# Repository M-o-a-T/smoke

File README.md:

# Fire Detector

## Gira

The "Gira" board is intended to plug into a "Gira Dual" smoke detector.
This device (30€) has a thermometer as well as a smoke chamber, a
serial interface that's actually useful, and the ability to run on 12V
external as well as 9V battery power.

It runs on 3.3V; the 1wire bus (5V) is connected via a level shifter.

Code will be in https://github.com/M-o-a-T/owslave

## Funk

The "Funk" board is a small (and currently untested) board that connects
a cheap smoke detector to RF. There's no code for it.

## Programming

The programming interface is a standard 6-pin plug, except that it's
used via a 3x2 pogo plug. If you need to attach a 6-pin header, soldering
that to the top of the pads is fairly easy. You should add some
two-component glue after soldering so that you won't pull the pads off when
you unplug.

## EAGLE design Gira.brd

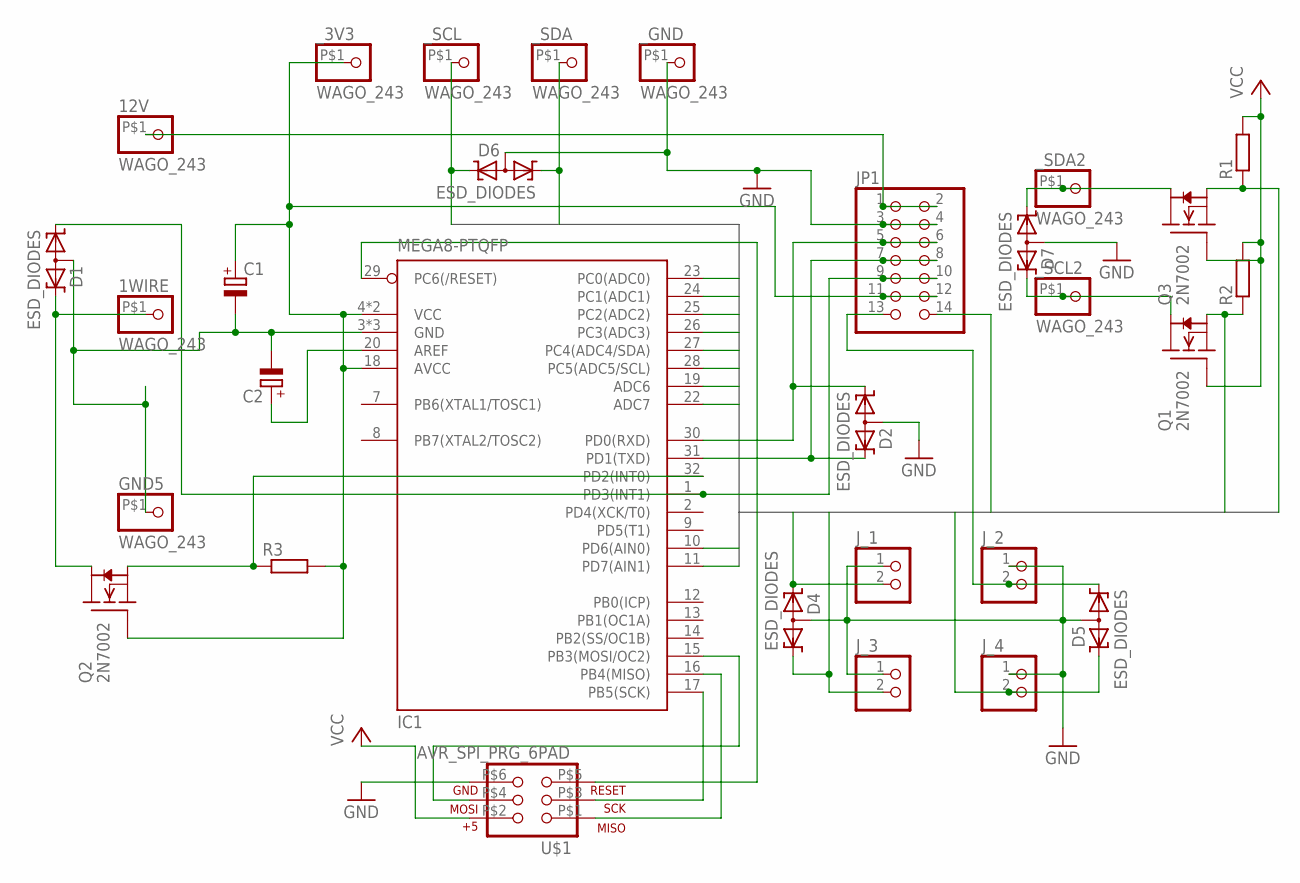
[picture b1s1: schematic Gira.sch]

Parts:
1WIRE, 12V: WAGO_243
C1, C2: CP1206
D1, D2, D4, D5, D6, D7: ESD_DIODES; SOT23
GND5: WAGO_243
IC1: MEGA8-PTQFP; TQFP32-08
JP1: PINHD-2X7; 2X07
J_1, J_2, J_3, J_4: PINHD-1X2LEVER; 1X02_GN
Q1, Q2, Q3: 2N7002; SOT23
R1, R2, R3: R-EU_R0603; R0603
U$1: AVR_SPI_PRG_6PAD; 2X3_PAD
_3V3: WAGO_243
_GND: WAGO_243
_SCL, _SCL2: WAGO_243
_SDA, _SDA2: WAGO_243

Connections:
3V3: C1.+, IC1.4 (VCC), IC1.6 (VCC), IC1.18 (AVCC), JP1.11, JP1.12, Q2.1 (G), R3.2, U$1.P$2 (2), _3V3.P$1
B1: D4.2 (K2), IC1.23 (PC0(ADC0)), J_1.2
B2: D5.1 (K1), IC1.24 (PC1(ADC1)), J_2.2
B3: D4.1 (K1), IC1.25 (PC2(ADC2)), J_3.2
B4: D5.2 (K2), IC1.26 (PC3(ADC3)), J_4.2
GND: C1.-, C2.-, D1.3 (AA), D2.3 (AA), D4.3 (AA), D5.3 (AA), D6.3 (AA), D7.3 (AA), GND5.P$1, IC1.3 (GND), IC1.5 (GND), IC1.21 (GND), JP1.3, JP1.4, J_1.1, J_2.1, J_3.1, J_4.1, U$1.P$6 (6), _GND.P$1
unnamed: C2.+, IC1.20 (AREF)
unnamed: IC1.32 (PD2(INT0)), Q2.2 (S), R3.1
unnamed: 1WIRE.P$1, D1.2 (K2), Q2.3 (D)
unnamed: D7.1 (K1), Q3.3 (D), _SDA2.P$1
unnamed: D7.2 (K2), Q1.3 (D), _SCL2.P$1
unnamed: IC1.15 (PB3(MOSI/OC2)), U$1.P$4 (4)
unnamed: IC1.16 (PB4(MISO)), U$1.P$1 (1)
unnamed: IC1.17 (PB5(SCK)), U$1.P$3 (3)
unnamed: IC1.29 (PC6(/RESET)), U$1.P$5 (5)
unnamed: 12V.P$1, JP1.1, JP1.2
unnamed: D2.2 (K2), IC1.31 (PD1(TXD)), JP1.7, JP1.8
unnamed: D2.1 (K1), IC1.30 (PD0(RXD)), JP1.5, JP1.6
unnamed: D1.1 (K1), IC1.1 (PD3(INT1)), JP1.9, JP1.10
RESET: IC1.10 (PD6(AIN0)), JP1.13
SCL: D6.2 (K2), IC1.22 (ADC7), _SCL.P$1
SCL2: IC1.28 (PC5(ADC5/SCL)), Q1.2 (S), R2.1
SDA: D6.1 (K1), IC1.19 (ADC6), _SDA.P$1
SDA2: IC1.27 (PC4(ADC4/SDA)), Q3.2 (S), R1.1
TEST: IC1.11 (PD7(AIN1)), JP1.14
VCC: Q1.1 (G), Q3.1 (G), R1.2, R2.2

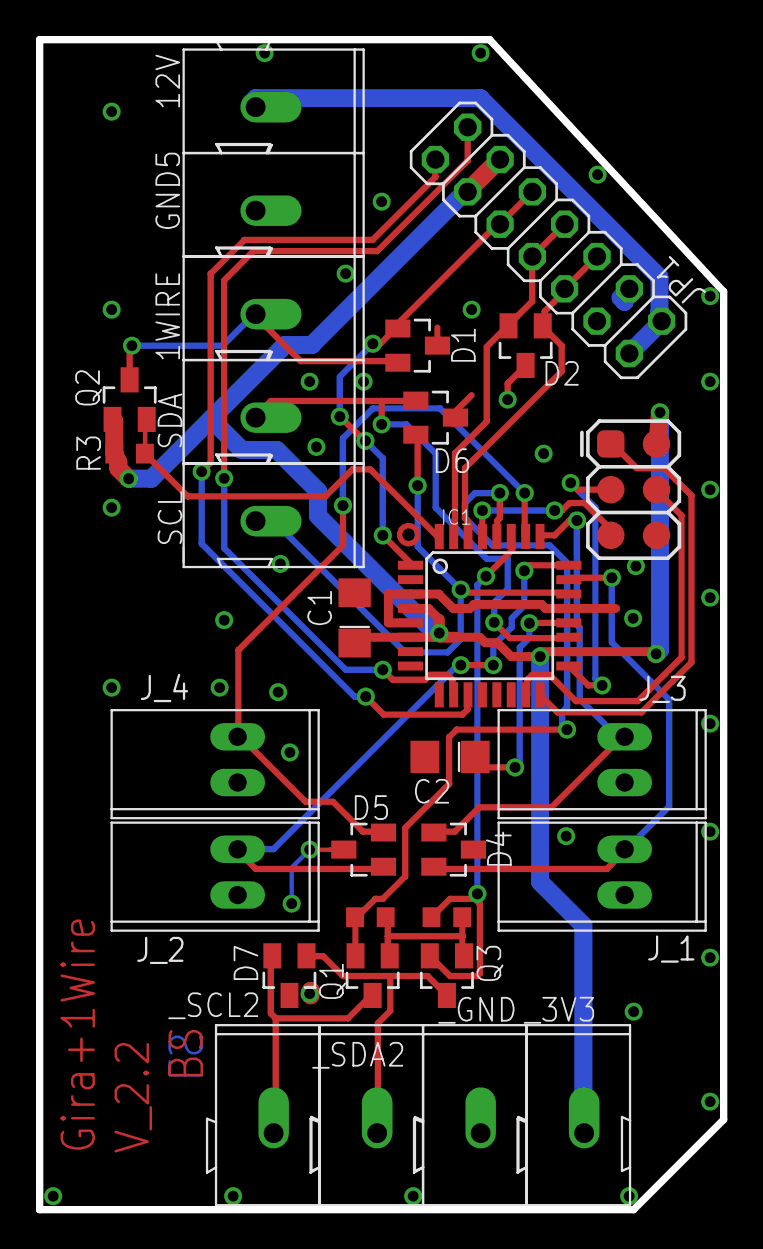
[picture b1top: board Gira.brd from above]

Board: 2 copper layers, 38.0 x 65.0 mm, 30 parts (0 on the bottom side), 26 nets.

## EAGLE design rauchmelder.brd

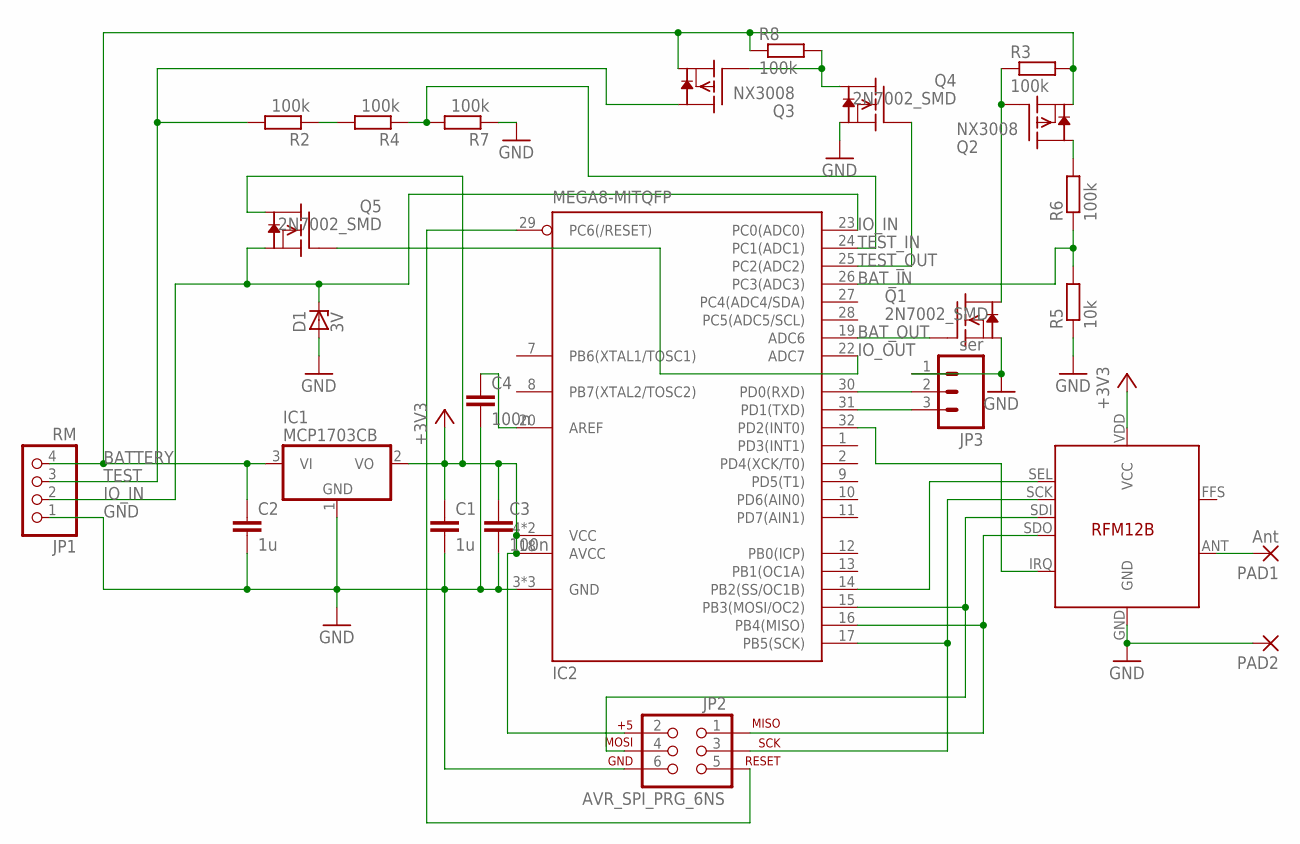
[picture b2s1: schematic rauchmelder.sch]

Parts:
C1, C2: 1u; C0603
C3, C4: 100n; C0603
D1: 3V; SOD80C
IC1: MCP1703CB; SOT23
IC2: MEGA8-MITQFP; TQFP32-08
IC3: RFM12B; MPN RFM12B-868-S1
JP1: RM; 1X04
JP2: AVR_SPI_PRG_6NS; 2X3-NS
JP3: ser; 1X03
PAD1: Ant; 1,6/0,8
PAD2: 1,6/0,8
Q1, Q4, Q5: 2N7002_SMD; SOT23
Q2, Q3: NX3008; SOT23; MPN NX3008NBK
R2, R3, R4, R6, R7, R8: 100k; R0603
R5: 10k; R0603

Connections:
+3V3: C1.1, C3.1, IC1.2 (VO), IC2.4 (VCC), IC2.6 (VCC), IC2.18 (AVCC), IC3.VDD (VCC), JP2.2, Q5.3 (D)
BATTERY: C2.1, IC1.3 (VI), JP1.4, Q2.2 (S), Q3.2 (S), R3.2, R8.1
BAT_IN: IC2.26 (PC3(ADC3)), R5.2, R6.1
BAT_OUT: IC2.19 (ADC6), Q1.1 (G)
GND: C1.2, C2.2, C3.2, C4.2, D1.A, IC1.1 (GND), IC2.3 (GND), IC2.5 (GND), IC2.21 (GND), IC3.GND, JP1.1, JP2.6, JP3.1, PAD2.1, Q1.2 (S), Q4.2 (S), R5.1, R7.1
IO_IN: D1.C, IC2.23 (PC0(ADC0)), JP1.2, Q5.2 (S)
IO_OUT: IC2.22 (ADC7), Q5.1 (G)
unnamed: R2.1, R4.2
unnamed: IC2.29 (PC6(/RESET)), JP2.5
unnamed: Q2.3 (D), R6.2
unnamed: IC2.16 (PB4(MISO)), IC3.SDO, JP2.1
unnamed: IC2.15 (PB3(MOSI/OC2)), IC3.SDI, JP2.4
unnamed: IC2.17 (PB5(SCK)), IC3.SCK, JP2.3
unnamed: IC2.14 (PB2(SS/OC1B)), IC3.SEL
unnamed: IC2.32 (PD2(INT0)), IC3.IRQ
unnamed: Q1.3 (D), Q2.1 (G), R3.1
unnamed: C4.1, IC2.20 (AREF)
unnamed: IC2.30 (PD0(RXD)), JP3.2
unnamed: IC2.31 (PD1(TXD)), JP3.3
unnamed: IC3.ANT, PAD1.1
unnamed: Q3.1 (G), Q4.3 (D), R8.2
TEST: JP1.3, Q3.3 (D), R2.2
TEST_IN: IC2.24 (PC1(ADC1)), R4.1, R7.2
TEST_OUT: IC2.25 (PC2(ADC2)), Q4.1 (G)

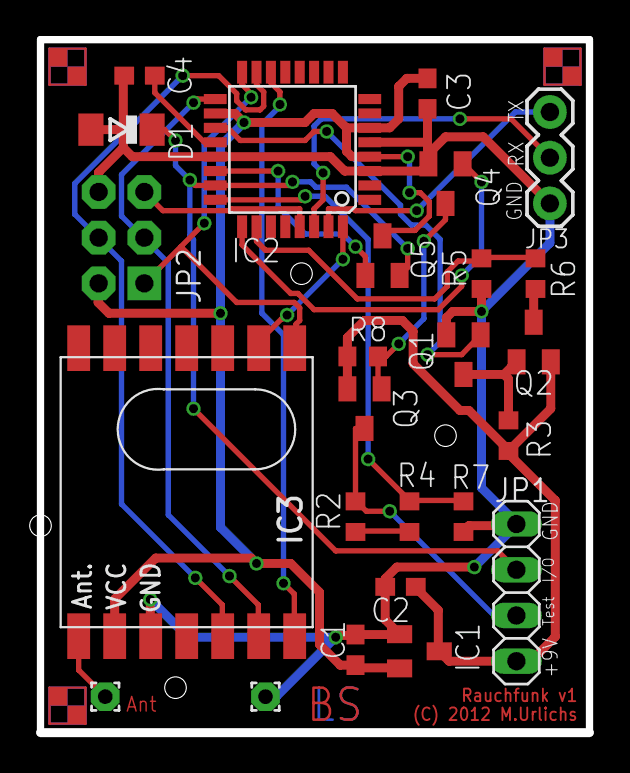
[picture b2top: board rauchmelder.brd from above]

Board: 2 copper layers, 30.5 x 38.5 mm, 28 parts (0 on the bottom side), 24 nets.

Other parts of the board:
U$1, U$2, U$3: FIDUCIAL

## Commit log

2015-02-16 .gitignore
2015-02-16 "final" versions
2015-02-16 Library
2015-02-28 Initial check-in of prototype
2015-03-01 Additional ground, I²C bus, input for light measurement
2015-03-01 renaming
2015-03-24 Update Gira
    min 0.3mm
    Klemmen gedreht
2015-03-24 Gira: längere Pads für CPU
2015-05-04 V2.1
    * Umstellung auf 3.3V (aus dem Rauchmelder)
    * keine Pullups am Port
2015-05-04 README
2015-05-11 V 2.2
    added Aref capacitor
    fixed power supply via prog connector problem
2015-06-03 V2.2

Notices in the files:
rauchmelder.brd:
(C) 2012 M.Urlichs
